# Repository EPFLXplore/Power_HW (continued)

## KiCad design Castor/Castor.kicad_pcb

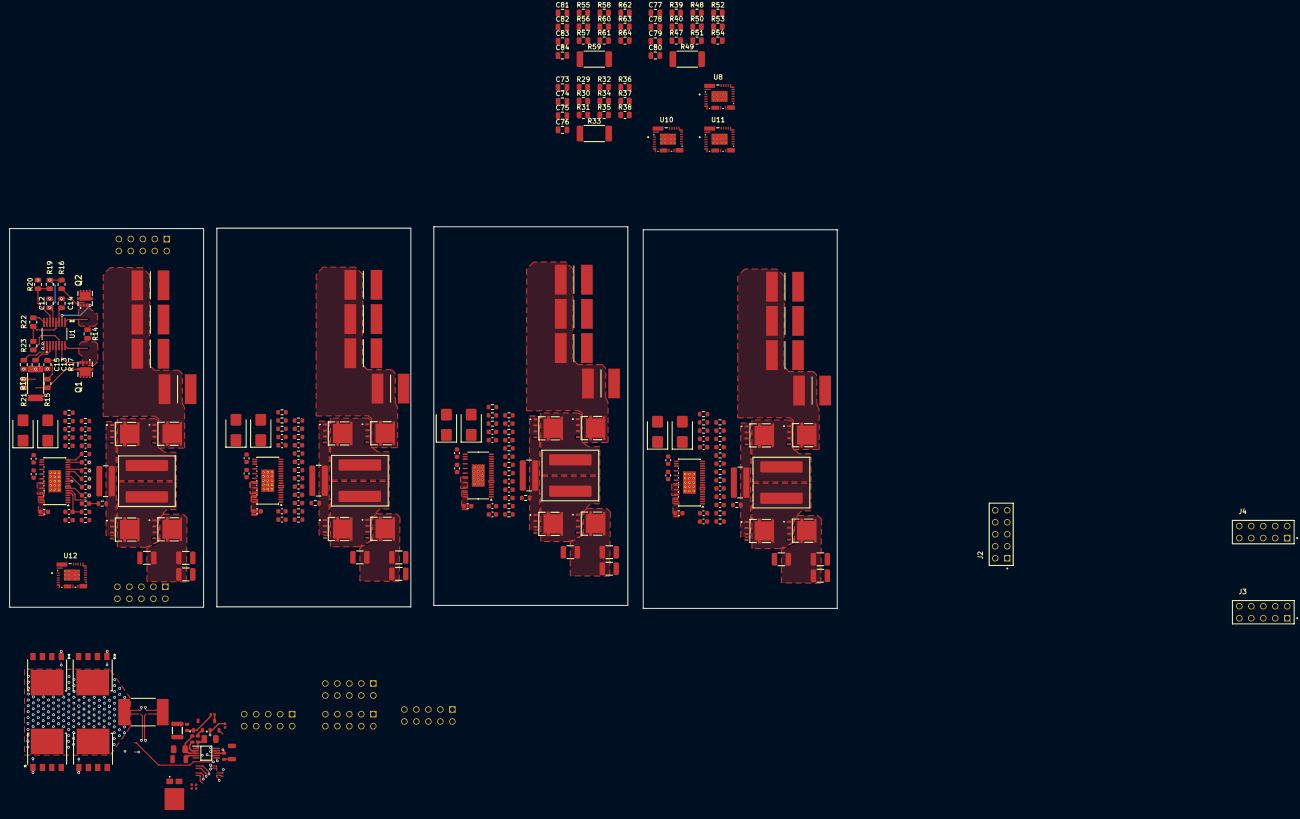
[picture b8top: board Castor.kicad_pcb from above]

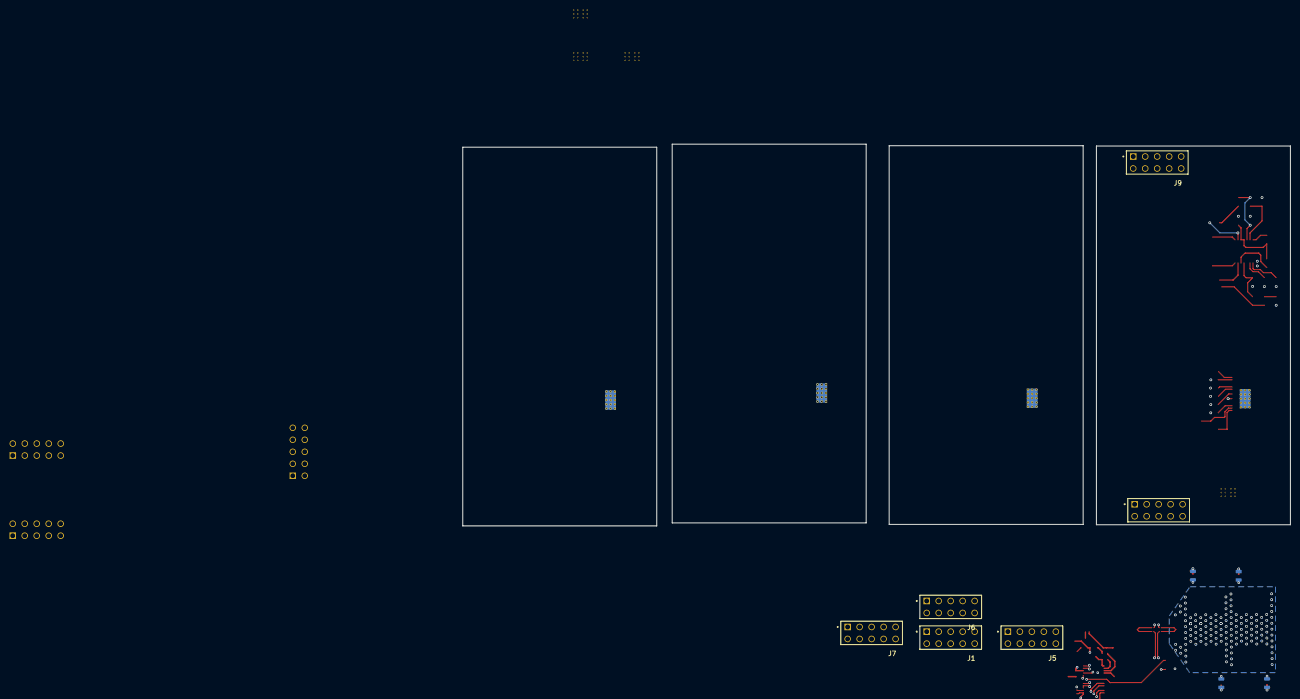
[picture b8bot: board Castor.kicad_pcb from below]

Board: 4 copper layers, 175.4 x 80.9 mm, 260 parts (10 on the bottom side), 158 nets.

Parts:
C2, C3, C4, C24, C25, C26, C37, C38, C39, C57, C58, C59: 10u; C_1210_3225Metric
C5, C27, C49, C60: 1u; C_0603_1608Metric
C6, C28, C53, C61: 100nF; C_0603_1608Metric
C7, C18, C20, C21, C22, C35, C40, C41, C42, C44, C54, C55, C68, C70, C71, C72: 100u T52M1107M035C0055; CAPC7360X200N
C8, C11, C29, C32, C47, C48, C62, C65: 220n; C_0603_1608Metric
C9, C10, C30, C31, C45, C46, C63, C64: 1n; C_0603_1608Metric
C12, C73, C77, C81: 1nF; C_0805_2012Metric
C13, C74, C78, C82: 1µF; C_0805_2012Metric
C14, C15, C75, C76, C79, C80, C83, C84: 100nF; C_0805_2012Metric
C16, C33, C50, C66: 0.1uF; C_0603_1608Metric
C17, C19, C34, C43, C51, C52, C67, C69: 4.7u; C_0603_1608Metric
C1103, C1504: 1u X7R 100V; C_0402_1005_DensityHigh
C1501: 10uF X7R 100V; C_1210_3225_DensityHigh
C1502: 2nF X7R 50V; C_1206_3216_DensityHigh
C1503: 110n X7R 100V; C_1206_3216_DensityHigh
CfbBot1, CfbBot2, CfbBot3, CfbBot4: 100n; C_0603_1608Metric
CfbTop1, CfbTop2, CfbTop3, CfbTop4: 100n; C_0603_1608Metric
Cth1, Cth2, Cth3, Cth4: 5.6n; C_0603_1608Metric
Cthp1, Cthp2, Cthp3, Cthp4: 56p; C_0603_1608Metric
D1, D2, D4, D5, D6, D7, D8, D9: MURS120; D_SMB
D1101: FSV10150V; FES10D
IC1501: TPS2490DGSRG4; SOP50P490X110-10N
J1, J3, J4, J5, J6, J7, J8, J9: IPS1-105-01-L-D; SAMTEC_IPS1-105-01-L-D
J2: IPT1-105-01-L-D; SAMTEC_IPT1-105-01-L-D
L1, L2, L3, L5: XAL1010-682MEB; L_Coilcraft_XAL1010-XXX
NT1101: NetTieShuntH; NetTie-2_SMD_Pad0.2mm
NT1103: NetTieShuntL; NetTie-2_SMD_Pad0.2mm
Q1, Q2: NVTFS5116PLTAG; NVTFS6H854NTAG
Q3, Q7, Q11, Q15: SQJ850EP; PowerPAK_SO-8
Q4, Q9, Q13, Q17: SQJ886EP; PowerPAK_SO-8
Q5, Q8, Q12, Q16: SQJ486EP; PowerPAK_SO-8
Q6, Q10, Q14, Q18: SQJ410EP; PowerPAK_SO-8
Q1101: SOT233 ZXMP10A13F; SOT-23-3
Q1102: SOT233 BSS123N; SOT-23-3
Q1201, Q1202, Q1203, Q1204: SQJQ186E-T1_GE3; POWERPAK8X8L_VIS
R1, R5, R6, R7, R11, R12, R13, R27, R28, R43, R44, R46: 2; R_0603_1608Metric
R2, R3, R8, R9, R24, R25, R41, R42: 10; R_0603_1608Metric
R4, R10, R26, R45: 4.02; R_0603_1608Metric
R14, R17, R19, R29, R32, R34, R39, R48, R50, R55, R58, R60: 332k; R_0805_2012Metric
R15, R21, R30, R36, R40, R52, R56, R62: 12k; R_0805_2012Metric
R16, R31, R47, R57: 10k; R_0805_2012Metric
R18, R33, R49, R59: 10m; R_2512_6332Metric_Pad1.40x3.35mm_HandSolder
R20, R35, R51, R61: 270k; R_0805_2012Metric
R22, R37, R53, R63: 100k; R_0805_2012Metric
R23, R38, R54, R64: 5.6k; R_0805_2012Metric
R1103: 47k 1% 1/10W; R_0603_1608_DensityHigh
R1104, R1105: 100k 1% 1/8W; R_0402_1005_DensityHigh
R1501: 212k 1% 1/10W; R_0603_1608_DensityHigh
R1502: 10k 1% 1/4W; R_1206_3216_DensityHigh_Large
R1503: 45k 1% 1/10W; R_0603_1608_DensityHigh
R1504: 7,5k 1% 1/4W; R_1206_3216_DensityHigh_Large
R1505: 0.3m; RES_WSLP3921_.003OHM_VIS
R1507: 1k 1% 1/10W; R_0603_1608_DensityHigh
R1601, R1602, R1603, R1604: 10R 1% 1/8W; R_0805_2012_DensityHigh
RfbBot1, RfbBot2, RfbBot3, RfbBot4: 5.11k; R_0603_1608Metric
RfbTop1, RfbTop2, RfbTop3, RfbTop4: 113k; R_0603_1608Metric
Rfreq1, Rfreq3, Rfreq5, Rfreq7: 100k; R_0603_1608Metric
Rfreq2, Rfreq4, Rfreq6, Rfreq8: 107k 1%; R_0603_1608Metric
Rsense2, Rsense3, Rsense5, Rsense7: 6m; R_1225_3264Metric
Rth1, Rth2, Rth3, Rth4: 9.31k; R_0603_1608Metric
U1: ADM1270ARQZ; RQ_16_ADI
U2, U3, U4, U9: LT8705AxFE; Linear_HTSSOP-31-38-1EP_4.4x9.7mm_P0.5mm_EP2.74x4.75mm_Ther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
U8, U10, U11, U12: TPS16851VMAR; IC_TPS16851VMAR

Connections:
/LT8705A1/ADM1270/VCAP: C74.1, R32.2, R34.2
/LT8705A1/ADM1270/Vout: R35.1, R37.1
/LT8705A1/BG1: Q8.2 (G), U2.17 (BG1)
/LT8705A1/BG2: R5.2, U2.19 (BG2)
/LT8705A1/BG2P: Q10.2 (G), R5.1
/LT8705A1/CSN: C10.1, R3.2, U2.5 (CSN)
/LT8705A1/CSNOUT: C18.1, C20.1, C21.1, C22.1, CfbTop2.1, Q9.1 (D), RfbTop2.1, U2.30 (EXTVCC), U2.32 (CSNOUT), U2.34 (CSPOUT)
/LT8705A1/CSP: C9.2, R2.2, U2.6 (CSP)
/LT8705A1/FBOUT: CfbBot2.1, CfbTop2.2, RfbBot2.1, RfbTop2.2, U2.9 (FBOUT)
/LT8705A1/INTVCC: C17.1, C19.1, R4.2, U2.1 (INTVCC), U2.18 (GATEVCC)
/LT8705A1/LDO: C16.1, U2.7 (LDO33), U2.8 (FBIN)
/LT8705A1/RT: Rfreq4.2, U2.15 (RT)
/LT8705A1/Rsense+: Q8.3 (S), Q10.3 (S), R2.1, Rsense3.2
/LT8705A1/SS: C6.1, U2.12 (SS)
/LT8705A1/SYNC: Rfreq3.2, U2.14 (SYNC)
/LT8705A1/TG1: R1.2, U2.26 (TG1)
/LT8705A1/TG1-: Q7.2 (G), R1.1
/LT8705A1/TG2: R6.2, U2.21 (TG2)
/LT8705A1/TG2-: Q9.2 (G), R6.1
/LT8705A1/VL_n: C11.2, L1.2, Q9.3 (S), Q10.1 (D), U2.22 (SW2)
/LT8705A1/VL_p: C8.1, L1.1, Q7.3 (S), Q8.1 (D), U2.24 (SW1)
/LT8705A1/Vc: Cth2.1, Cthp2.1, U2.11 (VC)
/LT8705A1/Vin: C2.1, C3.2, C4.2, C5.1, Q7.1 (D), U2.36 (CSNIN), U2.37 (CSPIN), U2.38 (VIN)
/LT8705A1/boost1: C8.2, D1.1 (K), U2.28 (BOOST1)
/LT8705A1/boost2: C11.1, D2.1 (K), U2.20 (BOOST2)
/LT8705A2/ADM1270/VCAP: C78.1, R48.2, R50.2
/LT8705A2/ADM1270/Vout: R51.1, R53.1
/LT8705A2/BG1: Q12.2 (G), U3.17 (BG1)
/LT8705A2/BG2: R11.2, U3.19 (BG2)
/LT8705A2/BG2P: Q14.2 (G), R11.1
/LT8705A2/CSN: C31.1, R9.2, U3.5 (CSN)
/LT8705A2/CSNOUT: C35.1, C44.1, C54.1, C55.1, CfbTop3.1, Q13.1 (D), RfbTop3.1, U3.30 (EXTVCC), U3.32 (CSNOUT), U3.34 (CSPOUT)
/LT8705A2/CSP: C30.2, R8.2, U3.6 (CSP)
/LT8705A2/FBOUT: CfbBot3.1, CfbTop3.2, RfbBot3.1, RfbTop3.2, U3.9 (FBOUT)
/LT8705A2/INTVCC: C34.1, C43.1, R10.2, U3.1 (INTVCC), U3.18 (GATEVCC)
/LT8705A2/LDO: C33.1, U3.7 (LDO33), U3.8 (FBIN)
/LT8705A2/RT: Rfreq6.2, U3.15 (RT)
/LT8705A2/Rsense+: Q12.3 (S), Q14.3 (S), R8.1, Rsense5.2
/LT8705A2/SS: C28.1, U3.12 (SS)
/LT8705A2/SYNC: Rfreq5.2, U3.14 (SYNC)
/LT8705A2/TG1: R7.2, U3.26 (TG1)
/LT8705A2/TG1-: Q11.2 (G), R7.1
/LT8705A2/TG2: R12.2, U3.21 (TG2)
/LT8705A2/TG2-: Q13.2 (G), R12.1
/LT8705A2/VL_n: C32.2, L2.2, Q13.3 (S), Q14.1 (D), U3.22 (SW2)
/LT8705A2/VL_p: C29.1, L2.1, Q11.3 (S), Q12.1 (D), U3.24 (SW1)
/LT8705A2/Vc: Cth3.1, Cthp3.1, U3.11 (VC)
/LT8705A2/Vin: C24.1, C25.2, C26.2, C27.1, Q11.1 (D), U3.36 (CSNIN), U3.37 (CSPIN), U3.38 (VIN)
/LT8705A2/boost1: C29.2, D4.1 (K), U3.28 (BOOST1)
/LT8705A2/boost2: C32.1, D5.1 (K), U3.20 (BOOST2)
/LT8705A3/ADM1270/VCAP: C82.1, R58.2, R60.2
/LT8705A3/ADM1270/Vout: R61.1, R63.1
/LT8705A3/BG1: Q16.2 (G), U4.17 (BG1)
/LT8705A3/BG2: R27.2, U4.19 (BG2)
/LT8705A3/BG2P: Q18.2 (G), R27.1
/LT8705A3/CSN: C64.1, R25.2, U4.5 (CSN)
/LT8705A3/CSNOUT: C68.1, C70.1, C71.1, C72.1, CfbTop4.1, Q17.1 (D), RfbTop4.1, U4.30 (EXTVCC), U4.32 (CSNOUT), U4.34 (CSPOUT)
/LT8705A3/CSP: C63.2, R24.2, U4.6 (CSP)
/LT8705A3/FBOUT: CfbBot4.1, CfbTop4.2, RfbBot4.1, RfbTop4.2, U4.9 (FBOUT)
/LT8705A3/INTVCC: C67.1, C69.1, R26.2, U4.1 (INTVCC), U4.18 (GATEVCC)
/LT8705A3/LDO: C66.1, U4.7 (LDO33), U4.8 (FBIN)
/LT8705A3/RT: Rfreq8.2, U4.15 (RT)
/LT8705A3/Rsense+: Q16.3 (S), Q18.3 (S), R24.1, Rsense7.2
/LT8705A3/SS: C61.1, U4.12 (SS)
/LT8705A3/SYNC: Rfreq7.2, U4.14 (SYNC)
/LT8705A3/TG1: R13.2, U4.26 (TG1)
/LT8705A3/TG1-: Q15.2 (G), R13.1
/LT8705A3/TG2: R28.2, U4.21 (TG2)
/LT8705A3/TG2-: Q17.2 (G), R28.1
/LT8705A3/VL_n: C65.2, L3.2, Q17.3 (S), Q18.1 (D), U4.22 (SW2)
/LT8705A3/VL_p: C62.1, L3.1, Q15.3 (S), Q16.1 (D), U4.24 (SW1)
/LT8705A3/Vc: Cth4.1, Cthp4.1, U4.11 (VC)
/LT8705A3/Vin: C57.1, C58.2, C59.2, C60.1, Q15.1 (D), U4.36 (CSNIN), U4.37 (CSPIN), U4.38 (VIN)
/LT8705A3/boost1: C62.2, D8.1 (K), U4.28 (BOOST1)
/LT8705A3/boost2: C65.1, D9.1 (K), U4.20 (BOOST2)
/LT8705A/ADM1270/PWRGD: R19.1, U1.14 (PWRGD)
/LT8705A/ADM1270/VCAP: C13.1, R17.2, R19.2, U1.3 (VCAP), U1.4 (ISET)
/LT8705A/ADM1270/Vin: Q1.5 (D_1), Q1.6 (D_2), Q1.7 (D_3), Q1.8 (D_4)
/LT8705A/ADM1270/Vout: Q2.5 (D_1), Q2.6 (D_2), Q2.7 (D_3), Q2.8 (D_4), R20.1, R22.1
/LT8705A/ADM1270/~FAULT: R17.1, U1.7 (ENABLE), U1.8 (*FAULT)
/LT8705A/BG1: Q5.2 (G), U9.17 (BG1)
/LT8705A/BG2: R43.2, U9.19 (BG2)
/LT8705A/BG2P: Q6.2 (G), R43.1
/LT8705A/CSN: C46.1, R42.2, U9.5 (CSN)
/LT8705A/CSNOUT: C7.1, C40.1, C41.1, C42.1, CfbTop1.1, Q4.1 (D), RfbTop1.1, U9.30 (EXTVCC), U9.32 (CSNOUT), U9.34 (CSPOUT)
/LT8705A/CSP: C45.2, R41.2, U9.6 (CSP)
/LT8705A/FBOUT: CfbBot1.1, CfbTop1.2, RfbBot1.1, RfbTop1.2, U9.9 (FBOUT)
/LT8705A/INTVCC: C51.1, C52.1, R45.2, U9.1 (INTVCC), U9.18 (GATEVCC)
/LT8705A/LDO: C50.1, U9.7 (LDO33), U9.8 (FBIN)
/LT8705A/RT: Rfreq2.2, U9.15 (RT)
/LT8705A/Rsense+: Q5.3 (S), Q6.3 (S), R41.1, Rsense2.2
/LT8705A/SS: C53.1, U9.12 (SS)
/LT8705A/SYNC: Rfreq1.2, U9.14 (SYNC)
/LT8705A/TG1: R44.2, U9.26 (TG1)
/LT8705A/TG1-: Q3.2 (G), R44.1
/LT8705A/TG2: R46.2, U9.21 (TG2)
/LT8705A/TG2-: Q4.2 (G), R46.1
/LT8705A/VL_n: C48.2, L5.2, Q4.3 (S), Q6.1 (D), U9.22 (SW2)
/LT8705A/VL_p: C47.1, L5.1, Q3.3 (S), Q5.1 (D), U9.24 (SW1)
/LT8705A/Vc: Cth1.1, Cthp1.1, U9.11 (VC)
/LT8705A/Vin: C37.1, C38.2, C39.2, C49.1, Q3.1 (D), U9.36 (CSNIN), U9.37 (CSPIN), U9.38 (VIN)
/LT8705A/boost1: C47.2, D6.1 (K), U9.28 (BOOST1)
/LT8705A/boost2: C48.1, D7.1 (K), U9.20 (BOOST2)
/Power - Precharge/PRE_D: NT1103.1, Q1201.5, Q1202.5, Q1203.5, Q1204.5, R1505.2
/Power - Precharge/PRE_EN: Q1102.1 (G), R1105.2
/Power - Precharge/PRE_G: IC1501.8 (GATE), R1507.1, R1601.2, R1602.1, R1603.2, R1604.1
/Power - Precharge/PRE_S: C1103.1, C1504.1, D1101.3 (K), IC1501.7 (OUT), Q1201.2, Q1201.3, Q1201.4, Q1202.2, Q1202.3, Q1202.4, Q1203.2, Q1203.3, Q1203.4, Q1204.2, Q1204.3, Q1204.4
/Power - Precharge/TIMER: C1502.1, IC1501.4 (TIMER)
/Power - Precharge/VBAT_IN: C1501.1, NT1101.2, Q1101.3 (D), R1103.2, R1505.1
/Power - Precharge/shunt+: IC1501.10 (VCC), NT1101.1
/Power - Precharge/shunt-: IC1501.9 (SENSE), NT1103.2
GND: C2.2, C3.1, C4.1, C5.2, C6.2, C7.2, C9.1, C10.2, C12.2, C13.2, C14.2, C15.2, C16.2, C17.2, C18.2, C19.2, C20.2, C21.2, C22.2, C24.2, C25.1, C26.1, C27.2, C28.2, C30.1, C31.2, C33.2, C34.2, C35.2, C37.2, C38.1, C39.1, C40.2, C41.2, C42.2, C43.2, C44.2, C45.1, C46.2, C49.2, C50.2, C51.2, C52.2, C53.2, C54.2, C55.2, C57.2, C58.1, C59.1, C60.2, C61.2, C63.1, C64.2, C66.2, C67.2, C68.2, C69.2, C70.2, C71.2, C72.2, C73.2, C74.2, C75.2, C76.2, C77.2, C78.2, C79.2, C80.2, C81.2, C82.2, C83.2, C84.2, C1103.2, C1501.2, C1502.2, C1503.2, C1504.2, CfbBot1.2, CfbBot2.2, CfbBot3.2, CfbBot4.2, Cthp1.2, Cthp2.2, Cthp3.2, Cthp4.2, D1101.1 (A_1), D1101.2 (A_2), IC1501.5 (GND), Q1102.2 (S), R3.1, R9.1, R16.2, R21.2, R23.2, R25.1, R31.2, R36.2, R38.2, R42.1, R47.2, R52.2, R54.2, R57.2, R62.2, R64.2, R1105.1, R1502.1, R1504.1, RfbBot1.2, RfbBot2.2, RfbBot3.2, RfbBot4.2, Rfreq1.1, Rfreq2.1, Rfreq3.1, Rfreq4.1, Rfreq5.1, Rfreq6.1, Rfreq7.1, Rfreq8.1, Rsense2.1, Rsense3.1, Rsense5.1, Rsense7.1, Rth1.2, Rth2.2, Rth3.2, Rth4.2, U1.9 (GND), U2.3 (IMON_IN), U2.10 (IMON_OUT), U2.16 (GND), U2.39 (GND), U3.3 (IMON_IN), U3.10 (IMON_OUT), U3.16 (GND), U3.39 (GND), U4.3 (IMON_IN), U4.10 (IMON_OUT), U4.16 (GND), U4.39 (GND), U9.3 (IMON_IN), U9.10 (IMON_OUT), U9.16 (GND), U9.39 (GND)
IN: U8.10 (IN), U8.22 (IN), U8.23 (IN), U8.24 (IN), U10.10 (IN), U10.22 (IN), U10.23 (IN), U10.24 (IN), U11.10 (IN), U11.22 (IN), U11.23 (IN), U11.24 (IN), U12.10 (IN), U12.22 (IN), U12.23 (IN), U12.24 (IN)
unnamed: C1503.1, R1507.2
unnamed: Cth1.2, Rth1.1
unnamed: Cth2.2, Rth2.1
unnamed: Cth3.2, Rth3.1
unnamed: Cth4.2, Rth4.1
unnamed: D1.2 (A), D2.2 (A), R4.1
unnamed: D4.2 (A), D5.2 (A), R10.1
unnamed: D6.2 (A), D7.2 (A), R45.1
unnamed: D8.2 (A), D9.2 (A), R26.1
unnamed: IC1501.1 (EN), R1501.1, R1502.2
unnamed: IC1501.3 (PROG), R1503.1, R1504.2
unnamed: IC1501.2 (VREF), R1503.2
unnamed: Q1.4 (G), U1.2 (RPFG)
unnamed: Q1.1 (S_1), Q1.2 (S_2), Q1.3 (S_3), R14.1, R18.1, U1.1 (VCC/SENSE+)
unnamed: Q2.4 (G), U1.15 (GATE)
unnamed: Q2.1 (S_1), Q2.2 (S_2), Q2.3 (S_3), R18.2, U1.16 (SENSE-)
unnamed: R29.1, R33.1
unnamed: R39.1, R49.1
unnamed: R55.1, R59.1
unnamed: Q1101.1 (G), R1103.1, R1104.2
unnamed: Q1101.2 (S), R1501.2
unnamed: Q1102.3 (D), R1104.1
unnamed: Q1201.1, R1601.1
unnamed: Q1202.1, R1603.1
unnamed: Q1203.1, R1604.2
unnamed: Q1204.1, R1602.2
unnamed: R22.2, R23.1, U1.12 (FB_PG)
unnamed: R20.2, R21.1, U1.13 (FLB)
unnamed: R15.2, R16.1, U1.6 (OV)
unnamed: C14.1, U1.10 (TIMER)
unnamed: C15.1, U1.11 (TIMER_OFF)
unnamed: C12.1, R14.2, R15.1, U1.5 (UV)
unnamed: R37.2, R38.1
unnamed: R35.2, R36.1
unnamed: R30.2, R31.1
unnamed: C73.1, R29.2, R30.1
unnamed: R53.2, R54.1
unnamed: R51.2, R52.1
unnamed: R40.2, R47.1
unnamed: C77.1, R39.2, R40.1
unnamed: R63.2, R64.1
unnamed: R61.2, R62.1
unnamed: R56.2, R57.1
unnamed: C81.1, R55.2, R56.1
OUT: U8.7 (OUT), U8.8 (OUT), U10.7 (OUT), U10.8 (OUT), U11.7 (OUT), U11.8 (OUT), U12.7 (OUT), U12.8 (OUT)

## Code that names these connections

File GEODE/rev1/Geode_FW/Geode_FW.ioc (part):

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Mcu.Name=STM32G483RETx
Mcu.Package=LQFP64
Mcu.UserName=STM32G483RETx
PA0.GPIOParameters=GPIO_Label
PA0.GPIO_Label=FAULT1_B
PA0.Signal=GPIO_Input
PA1.GPIOParameters=GPIO_Label
PA1.GPIO_Label=MB_SHDN_VA
PA1.Signal=GPIO_Output
PA10.GPIOParameters=GPIO_Label
PA10.GPIO_Label=RUN1_A
PA10.Signal=GPIO_Input
PA11.Mode=Device
PA11.Signal=USB_DM
PA12.Mode=Device
PA12.Signal=USB_DP
PA13.Mode=Trace_Asynchronous_SW
PA13.Signal=SYS_JTMS-SWDIO
PA14.Mode=Trace_Asynchronous_SW
PA14.Signal=SYS_JTCK-SWCLK
PA15.Mode=NSS_Signal_Hard_Output
PA15.Signal=SPI3_NSS
PA2.GPIOParameters=GPIO_Label
PA2.GPIO_Label=ALERT_B
PA2.Signal=GPIO_Input
PA3.GPIOParameters=GPIO_Label
PA3.GPIO_Label=MB_SHDN_VB
PA3.Signal=GPIO_Output
PA4.Mode=NSS_Signal_Hard_Output
PA4.Signal=SPI1_NSS
PA5.Mode=Full_Duplex_Master
PA5.Signal=SPI1_SCK
PA6.Mode=Full_Duplex_Master
PA6.Signal=SPI1_MISO
PA7.Mode=Full_Duplex_Master
PA7.Signal=SPI1_MOSI
PA8.Mode=I2C
PA8.Signal=I2C2_SDA
PA9.Mode=I2C
PA9.Signal=I2C2_SCL
PB0.GPIOParameters=GPIO_Label
PB0.GPIO_Label=PRE_EN
PB0.Signal=GPIO_Output
PB1.GPIOParameters=GPIO_Label
PB1.GPIO_Label=FAN_CTRL
PB1.Signal=GPIO_Output
PB10.GPIOParameters=GPIO_Label
PB10.GPIO_Label=FAULT1_A
PB10.Signal=GPIO_Input
PB11.GPIOParameters=GPIO_Label
PB11.GPIO_Label=TEMP_SENS
PB11.Signal=GPIO_Analog
PB12.Mode=NSS_Signal_Hard_Output
PB12.Signal=SPI2_NSS
PB13.Mode=Full_Duplex_Master
PB13.Signal=SPI2_SCK
PB14.Mode=Full_Duplex_Master
PB14.Signal=SPI2_MISO
PB15.Mode=Full_Duplex_Master
PB15.Signal=SPI2_MOSI
PB2.GPIOParameters=GPIO_Label
PB2.GPIO_Label=MA_SHDN_VA
PB2.Signal=GPIO_Output
PB3.Mode=Trace_Asynchronous_SW
PB3.Signal=SYS_JTDO-SWO
PB4.GPIOParameters=GPIO_Label
PB4.GPIO_Label=FAULT0_A
PB4.Signal=GPIO_Input
PB5.Mode=FDCAN_Activate
PB5.Signal=FDCAN2_RX
PB6.Mode=FDCAN_Activate
PB6.Signal=FDCAN2_TX
PB7.GPIOParameters=GPIO_Label
PB7.GPIO_Label=FAULT1_A
PB7.Signal=GPIO_Output
PB8-BOOT0.Mode=FDCAN_Activate
PB8-BOOT0.Signal=FDCAN1_RX
PB9.Mode=FDCAN_Activate
PB9.Signal=FDCAN1_TX
PC0.GPIOParameters=GPIO_Label
PC0.GPIO_Label=IRQ
PC0.Signal=GPIO_Output
PC1.GPIOParameters=GPIO_Label
PC1.GPIO_Label=SYNC0
PC1.Signal=GPIO_Output
PC10.Mode=Full_Duplex_Master
PC10.Signal=SPI3_SCK
PC11.Mode=Full_Duplex_Master
PC11.Signal=SPI3_MISO
PC12.Mode=Full_Duplex_Master
PC12.Signal=SPI3_MOSI
PC13.GPIOParameters=GPIO_Label
PC13.GPIO_Label=LED_CAT1
PC13.Signal=GPIO_Output
PC14-OSC32_IN.GPIOParameters=GPIO_Label
PC14-OSC32_IN.GPIO_Label=LED_CAT2
PC14-OSC32_IN.Signal=GPIO_Output
PC15-OSC32_OUT.GPIOParameters=GPIO_Label
PC15-OSC32_OUT.GPIO_Label=RUN1_B
PC15-OSC32_OUT.Signal=GPIO_Input
PC2.GPIOParameters=GPIO_Label
PC2.GPIO_Label=SYNC1
PC2.Signal=GPIO_Output
PC3.GPIOParameters=GPIO_Label
PC3.GPIO_Label=RUN0_B
PC3.Signal=GPIO_Input
PC4.GPIOParameters=GPIO_Label
PC4.GPIO_Label=FAULT0_B
PC4.Signal=GPIO_Input
PC5.GPIOParameters=GPIO_Label
PC5.GPIO_Label=PRE_FLT
PC5.Signal=GPIO_Input
PC6.GPIOParameters=GPIO_Label
PC6.GPIO_Label=RUN0_A
PC6.Signal=GPIO_Input
PC7.GPIOParameters=GPIO_Label
PC7.GPIO_Label=INT
PC7.Signal=GPIO_Output
PC8.Mode=I2C
PC8.Signal=I2C3_SCL
PC9.Mode=I2C
PC9.Signal=I2C3_SDA
PD2.GPIOParameters=GPIO_Label
PD2.GPIO_Label=ALERT_A
PD2.Signal=GPIO_Input
PF0-OSC_IN.Mode=HSE-External-Oscillator
PF0-OSC_IN.Signal=RCC_OSC_IN
PF1-OSC_OUT.Mode=HSE-External-Oscillator
PF1-OSC_OUT.Signal=RCC_OSC_OUT
RCC.HSE_VALUE=48000000
RCC.SYSCLKFreq_VALUE=144000000
RCC.SYSCLKSource=RCC_SYSCLKSOURCE_PLLCLK
board=custom

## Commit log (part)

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2025-02-28 Initial Battman commit, schema ~30%
2025-03-02 updated schematics, LTCs finished begin of MCU
2025-03-04 MCU Schematic progress
2025-03-05 MCU schematic updates
2025-03-06 renamed aux supply
2025-03-09 Added photos, updated to Kicad 9.0 and wrote next improvements
2025-03-10 Removed unnecessary files
2025-03-10 Added documentation folder, imroved documentation, added fabrication and manufacturing documents
2025-03-10 Removed .DS_Store file and updated .gitignore
2025-03-12 Powerpath advances
2025-03-17 Schema comlete(enfin j'espère)
2025-03-17 Schematics cleaned up, pdf created
2025-03-20 Schematic update
2025-03-21 small fixes on schematics
2025-03-21 updated KiCad
2025-03-22 Updated STEP file and added fan 3D model
2025-03-25 Updated Schematics
2025-03-25 Uopdated Schematics fixed
2025-03-27 Intermediate BMS Backup
2025-04-02 Layout Backup, only MCU missing
2025-04-04 layout progress
2025-04-06 Layout finished (kind of)
2025-04-07 BMS Layout Finished, not reviewed
2025-04-07 Layout finished, not reviewed yet
2025-04-07 Layout updated with teardrops
2025-04-08 fixed soldermask
2025-04-08 Added fan header
2025-04-13 Improved Doc and added thermal images
2025-04-22 Implemented Com isolation and fixes from reviews
2025-04-22 added month to PCB
2025-04-29 Final fixes, updated gerber
2025-05-04 Begin of kicad conversion
2025-05-08 Changed component name scheme to simplify kicad conversion
2025-06-01 Altium Schema modified for KiCad conversion
2025-06-01 kicad release
2025-06-08 Last changes before v1.1
2025-06-10 Added all libraries to git
2025-07-14 Done with changes of v1.1, need to final check and order
2025-07-24 Finished V1.1, maybe extra cleaning needed of some details in the doc
2025-08-14 pollux motherboard altium files
2025-08-14 added high power module
2025-08-14 high power kicad
2025-08-14 pollux Altium
2025-08-14 added pollux and lv module
2025-08-28 Small adjustments
2025-09-04 Cleaned README, updated block diagram
2025-09-28 Initial changes
2025-10-04 changed connectors, removed can, added fuse, disconnected EXTVCC in power generation
2025-10-08 replaced output connectors, added UART connector, removed fuse - schematics
2025-10-12 updated layout with USART and SWD connector
2025-10-12 added XT30 moved usbC for more space
2025-10-13 added xt30 connectors to layout moved screw holes
2025-10-16 Create README.md for Bucky
2025-10-16 Uploaded Bucky V1
    Bucky V1 schematics and layout
2025-10-18 Added silkscreen and mounting holes to PCB, improved layout
2025-10-18 fixed xt60 polarity connection
2025-10-22 spaced vertical connectors, added 40A fuse
2025-10-22 added 4 screws, switched motout and batt in
2025-11-01 added features from GEODE to the schematics
2025-11-06 adapted schematics and added more protection from GEODE (Reverse Current)
2025-11-08 upadated scchematics
2025-11-09 changed high power transistors, started layout
2025-11-11 removed 12V local generation
2025-11-15 created Bucky++ with new template and e-fuses
2025-11-15 added over-current protection on main input
2025-11-16 fixed errors and added protection diodes
2025-11-17 fixed issues after Pedro's review
2025-11-19 final version before review
2025-11-21 initial component placement
2025-11-23 worked on layout, added adm1270
2025-11-24 implemented ADM1270 (no foldback yet
2025-11-24 implemented foldback
2025-11-30 more routing
2025-11-30 finished routing
2025-12-05 wider planes, USB impedance matching
2025-12-17 changed PMOS transistor for a larger one
2026-01-06 updated ADM1270 circuit
2026-01-07 improved layout and silkscreen
2026-01-24 updated circuit after review. updated silkscreen
2026-01-24 added computations spreadsheets and fixed mistake in schematics
2026-02-08 fixed second review comment
2026-02-09 fix layout and tolerance issues, started working on routing alerts
2026-02-09 connected alert pins of each rail
2026-02-09 revised some decoupling capacitors
2026-02-10 Cleared DRC errors, corrected routing errors, cleaned the schematic
2026-02-10 final fixes in layout, adjusted screw holes
2026-02-10 removed some warnings
2026-02-10 linked library to remove some more warnings
2026-02-10 Added ioc
2026-02-15 manufacturing contraints not being detected
2026-02-15 added computations for layout, fixed a few issues
2026-02-16 fixed a few issues with Power/GND planes
2026-02-16 Last cleaning and checks, new gerber, buying
2026-03-17 created draft of BuckyHat
2026-03-21 worked on layout
2026-03-23 layout almost done
2026-03-28 no DRC errors
2026-03-28 spaghetti
2026-03-29 fixed en bug
2026-04-12 Icky
2026-04-12 ERC passed
2026-04-12 ERC passed v2
2026-04-13 routing
2026-04-14 Shite done
2026-04-16 castor
2026-04-16 added power hat
2026-04-16 added power changes
2026-04-18 added gerbers and final modifications before ordering
2026-05-17 Board ready to review
2026-05-18 Board ready for REV2
2026-05-18 Board ready for REV2 (added notes)
2026-06-24 Added Pedro's name
2026-06-24 added monitoring, rerouting partially
